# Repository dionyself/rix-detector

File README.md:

# RIX Detector
Yet another DIY metal detector.

.. image:: https://raw.githubusercontent.com/dionyself/rix-detector/master/images/rix_kicad_view.png
   :height: 100px
   :width: 200 px
   :scale: 50 %
   :alt: alternate text
   :align: right

Bitcoin Donations.

.. image:: https://raw.githubusercontent.com/dionyself/golang-cms/master/static/img/btttcc.png

XMR (Monero) Donations.

.. image:: https://raw.githubusercontent.com/dionyself/golang-cms/master/static/img/xmmr.jpeg
   :height: 300px
   :width: 300 px

Paypal

.. image:: https://www.paypalobjects.com/en_US/i/btn/btn_donateCC_LG.gif
   :height: 100px
   :width: 200 px
   :scale: 50 %
   :alt: alternate text
   :align: right
   :target: https://www.paypal.com/cgi-bin/webscr?cmd=_s-xclick&hosted_button_id=L4H5TUWZTZERS

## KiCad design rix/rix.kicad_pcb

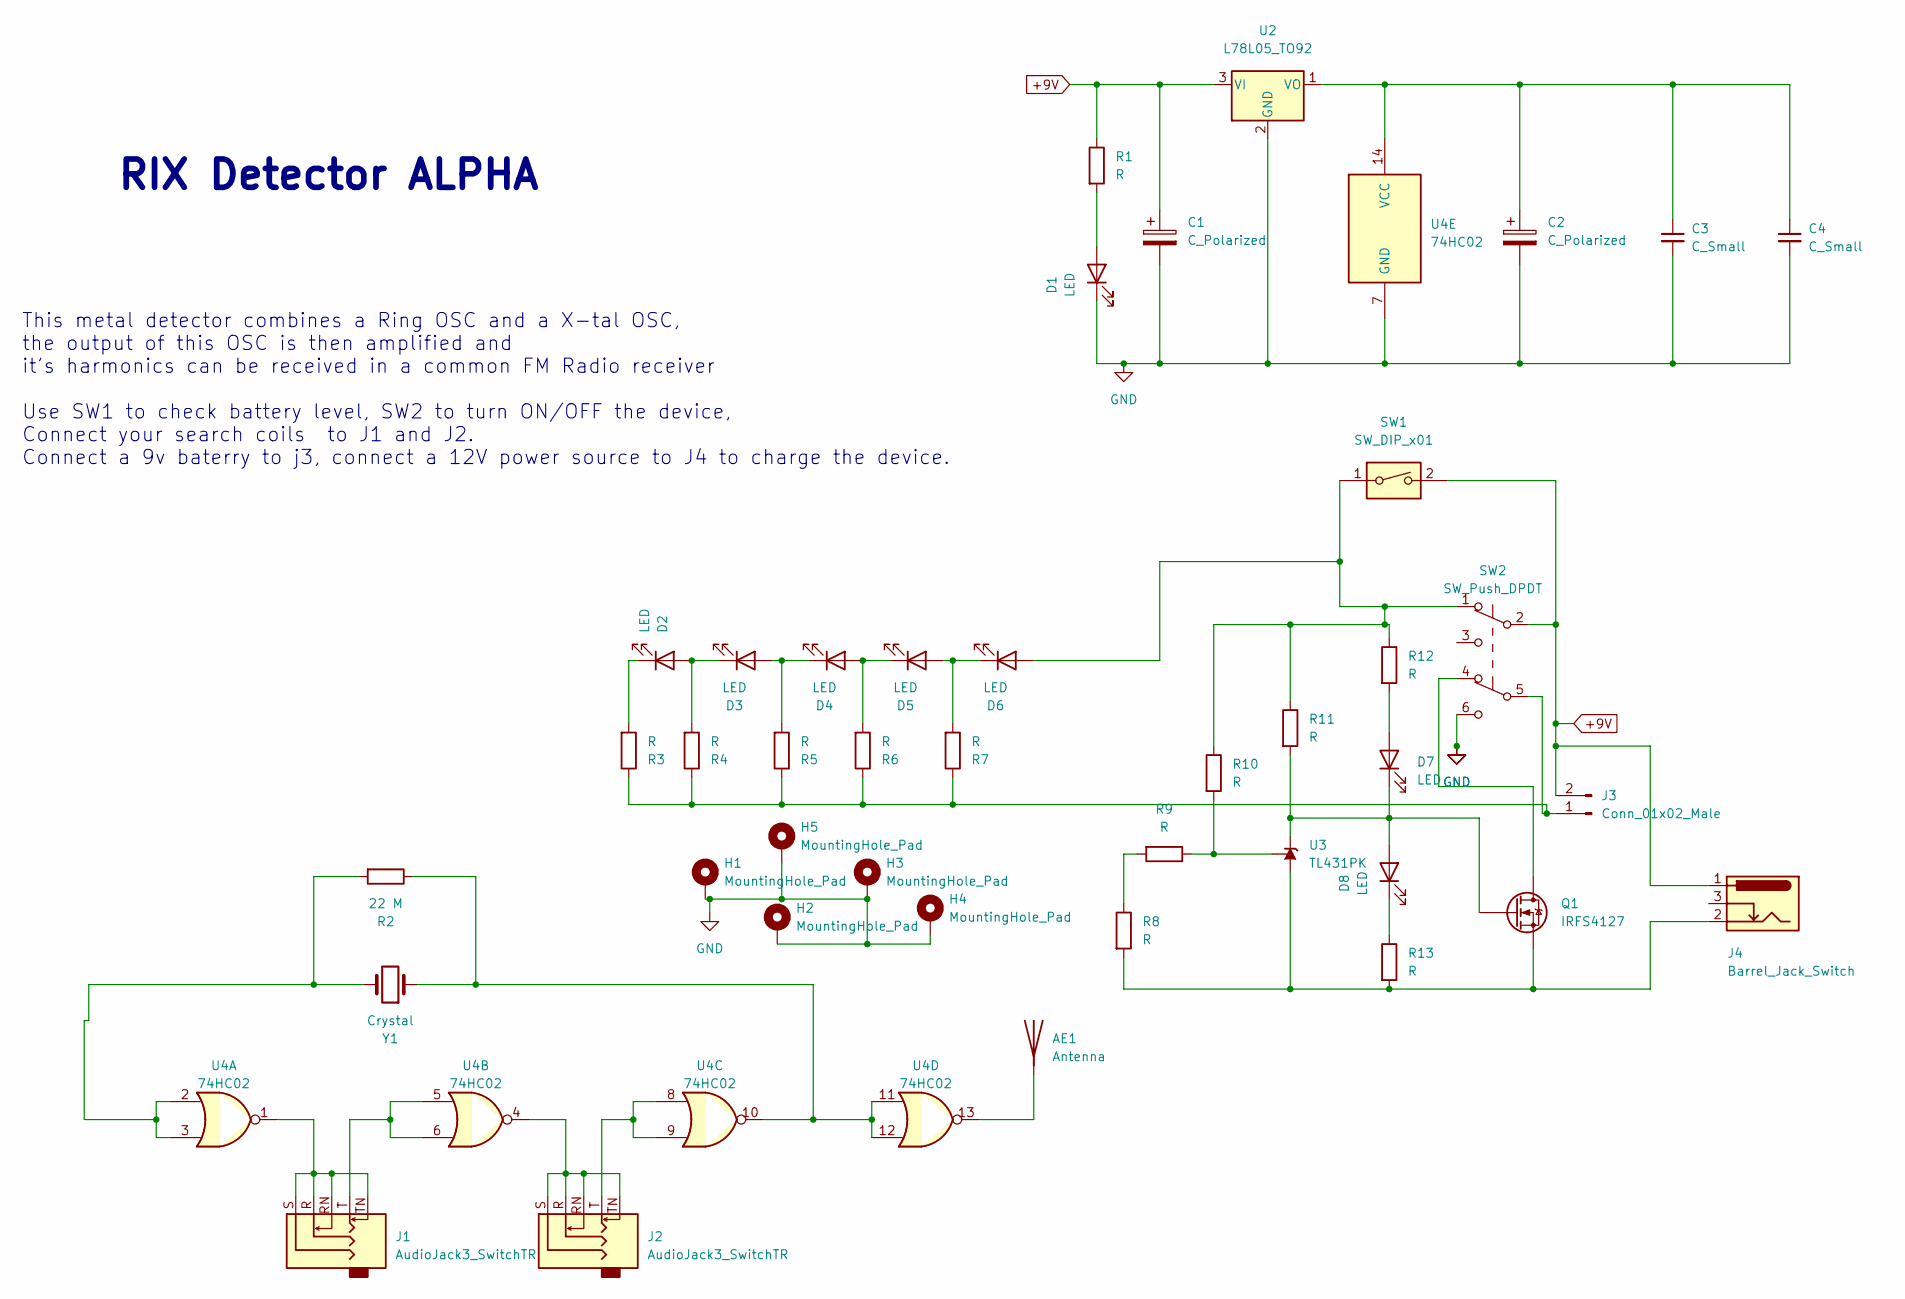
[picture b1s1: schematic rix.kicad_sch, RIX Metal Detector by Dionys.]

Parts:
AE1: Antenna; PinHeader_1x01_P1.00mm_Vertical
C1, C2: C_Polarized; CP_Radial_D6.3mm_P2.50mm
C3, C4: C_Small; C_Disc_D3.8mm_W2.6mm_P2.50mm
D1, D2, D3, D4, D5, D6, D7, D8: LED; LED_D3.0mm
H1, H2, H3, H4, H5: MountingHole_Pad; MountingHole_2.2mm_M2_DIN965_Pad_TopBottom
J1, J2: AudioJack3_SwitchTR; Jack_3.5mm_Ledino_KB3SPRS_Horizontal
J3: Conn_01x02_Male; JST_XH_B2B-XH-A_1x02_P2.50mm_Vertical
J4: Barrel_Jack_Switch; BarrelJack_Horizontal
Q1: IRFS4127; TO-92_Wide
R1, R3, R4, R5, R6, R7, R8, R9, R10, R11, R12, R13: R; R_Axial_DIN0204_L3.6mm_D1.6mm_P5.08mm_Horizontal
R2: 22 M; R_Axial_DIN0204_L3.6mm_D1.6mm_P5.08mm_Horizontal
SW1: SW_DIP_x01; SW_PUSH_6mm_H5mm
SW2: SW_Push_DPDT; SW_Push_2P2T_Toggle_CK_PVA2OAH5xxxxxxV2
U2: L78L05_TO92; TO-92_Wide
U3: TL431PK; TO-92_Wide
U4: 74HC02; DIP-14_W7.62mm
Y1: Crystal; Crystal_HC49-4H_Vertical

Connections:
+9V: C1.1, J3.2, J4.1, R1.1, SW1.2, SW2.2 (B), U2.3 (VI)
GND: C1.2, C2.2, C3.2, C4.2, D1.1 (K), H1.1, H2.1, H3.1, H4.1, H5.1, SW2.6 (C), U2.2 (GND), U4.7 (GND)
unnamed: AE1.1 (A), U4.13
unnamed: D1.2 (A), R1.2
unnamed: D2.2 (A), D3.1 (K), R4.2
unnamed: D2.1 (K), R3.2
unnamed: D3.2 (A), D4.1 (K), R5.2
unnamed: D4.2 (A), D5.1 (K), R6.2
unnamed: D5.2 (A), D6.1 (K), R7.2
unnamed: D6.2 (A), R10.1, R11.1, R12.1, SW1.1, SW2.1 (A)
unnamed: D7.2 (A), R12.2
unnamed: D7.1 (K), D8.2 (A), Q1.1 (G), R11.2, U3.3 (K)
unnamed: D8.1 (K), R13.1
unnamed: J1.R, J1.RN, J1.S, J1.TN, U4.1
unnamed: J1.T, U4.5, U4.6
unnamed: J2.R, J2.RN, J2.S, J2.TN, U4.4
unnamed: J2.T, U4.8, U4.9
unnamed: J3.1, R3.1, R4.1, R5.1, R6.1, R7.1, SW2.5 (B)
unnamed: Q1.2 (D), SW2.4 (A)
unnamed: J4.2, Q1.3 (S), R8.2, R13.2, U3.2 (A)
unnamed: R2.1, U4.10, U4.11, U4.12, Y1.1
unnamed: R2.2, U4.2, U4.3, Y1.2
unnamed: R8.1, R9.2
unnamed: C2.1, C3.1, C4.1, U2.1 (VO), U4.14 (VCC)
unnamed: R9.1, R10.2, U3.1 (REF)

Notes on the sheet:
This metal detector combines a Ring OSC and a X-tal OSC, the output of this OSC is then amplified and it's harmonics can be received in a common FM Radio receiver Use SW1 to check battery level, SW2 to turn ON/OFF the device, Connect your search coils to J1 and J2. Connect a 9v baterry to j3, conne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
RIX Detector ALPHA

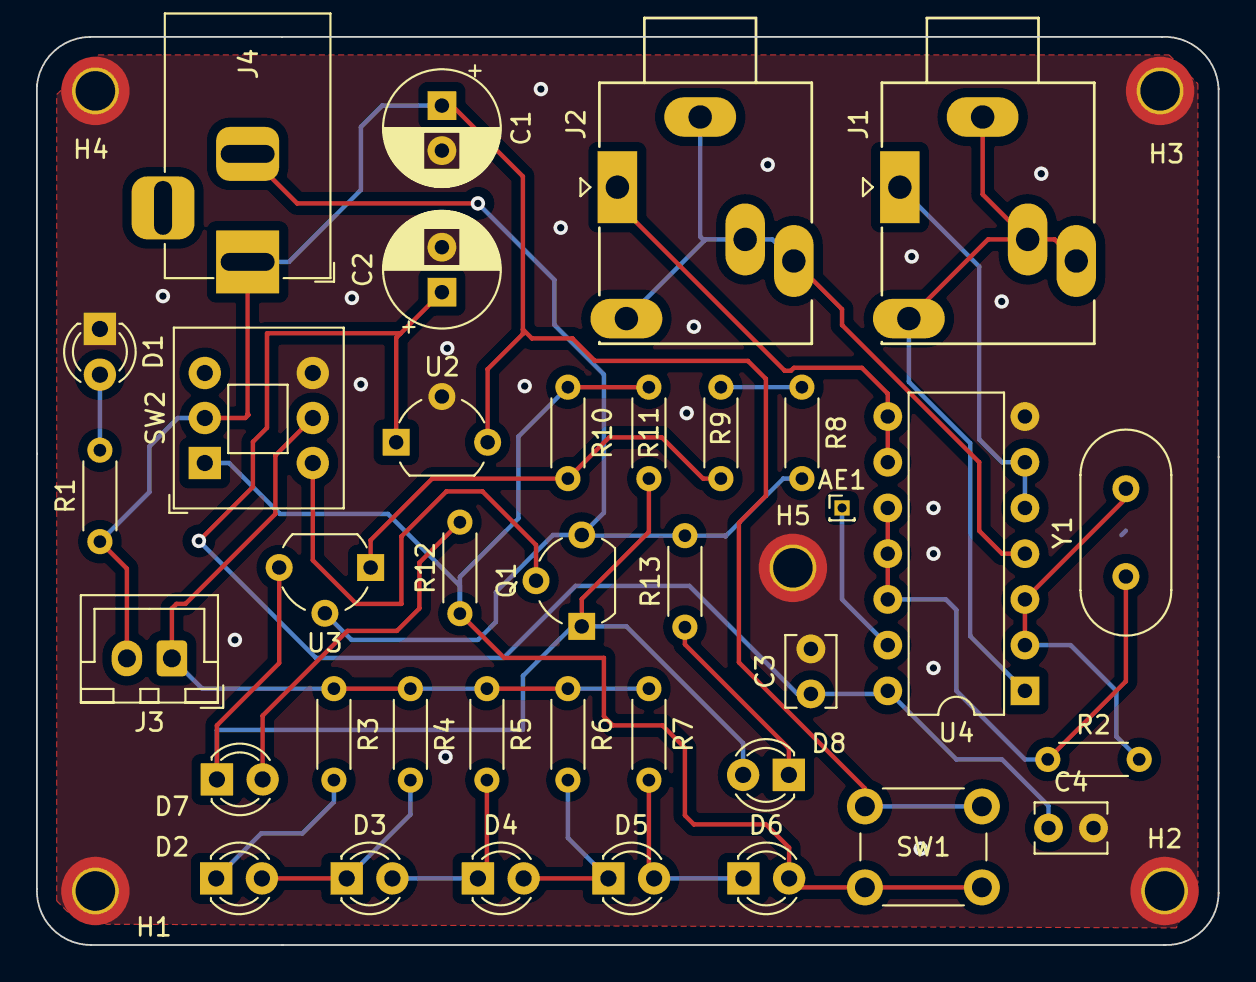
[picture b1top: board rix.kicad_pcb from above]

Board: 2 copper layers, 65.7 x 50.5 mm, 42 parts (0 on the bottom side), 25 nets.

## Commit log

2022-11-18 Adding circuit schematics
2022-11-21 PCB improvements
2022-11-22 Adding tracks
2022-11-22 Rename README.md to README.rst
2022-11-23 Docs
2022-11-24 Adding gerber files
2022-11-28 Updating board constraits
2022-12-01 Update gerber files
2022-12-01 Updating board labels
2022-12-08 Updating gerber files
2023-02-27 Uptating req Kicad7
